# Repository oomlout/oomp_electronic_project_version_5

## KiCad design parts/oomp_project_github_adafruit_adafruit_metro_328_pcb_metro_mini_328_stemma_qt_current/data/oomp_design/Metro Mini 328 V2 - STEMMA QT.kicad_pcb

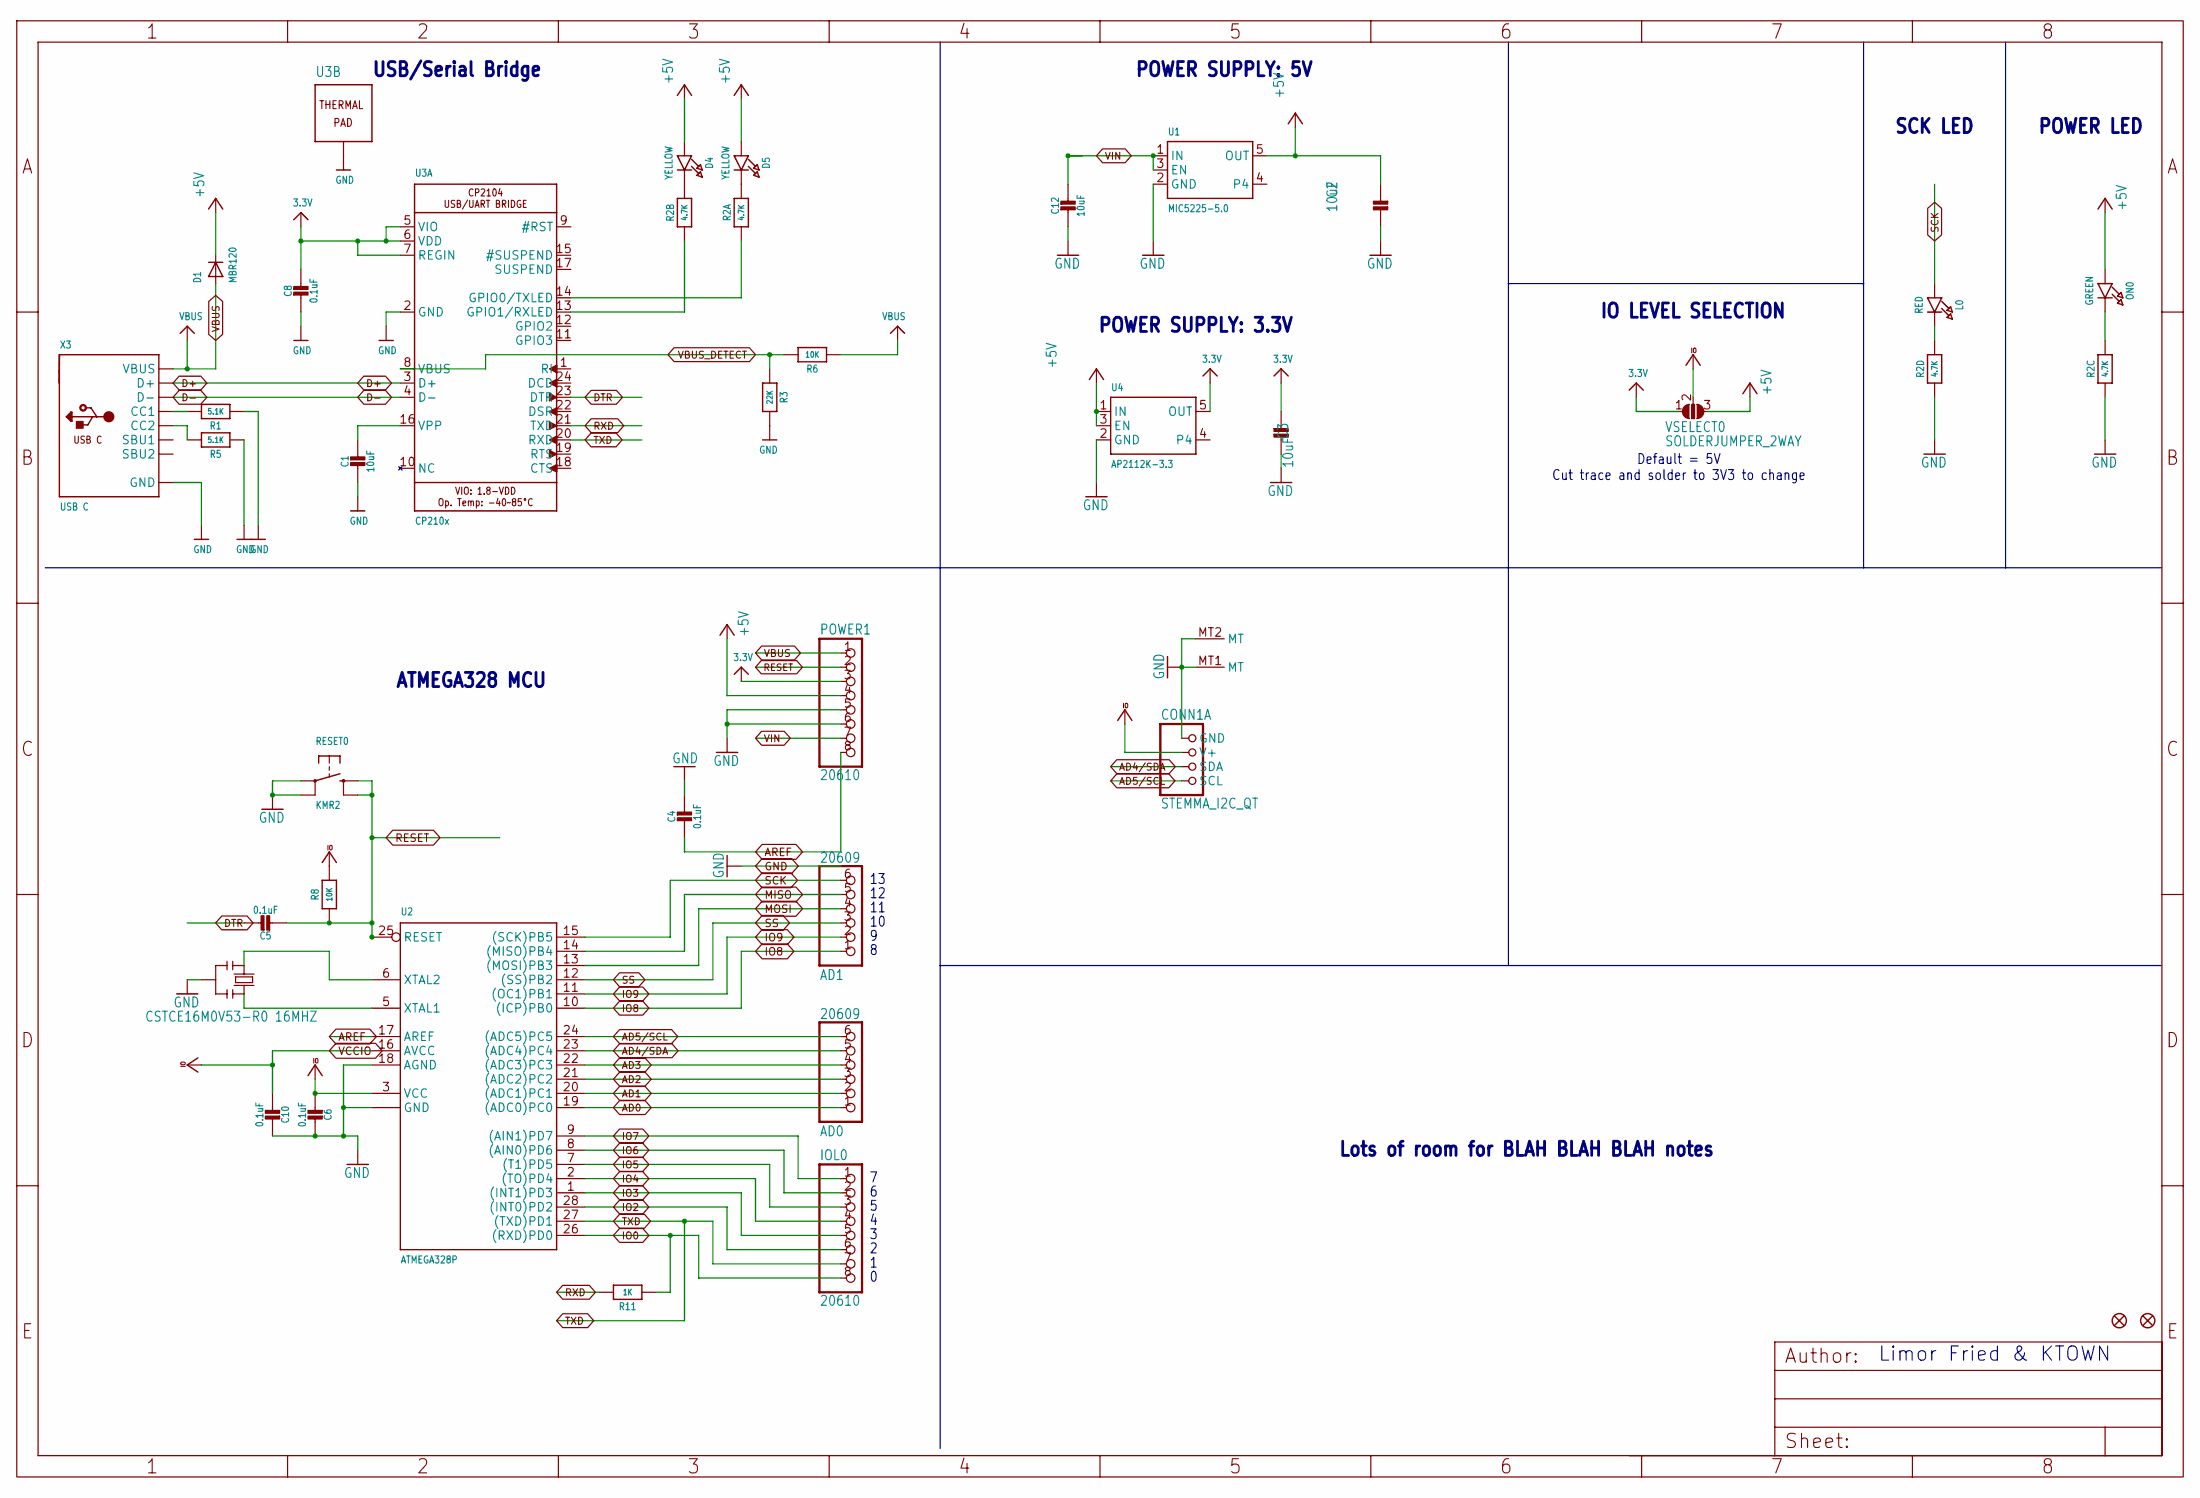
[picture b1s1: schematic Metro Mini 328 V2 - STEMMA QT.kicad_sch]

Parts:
AD0, AD1: 20609; 1X06_ROUND
C1, C2, C3, C12: 10uF; 0805-NO
C4, C5, C6, C8, C10: 0.1uF; 0603-NO
CONN1: STEMMA_I2C_QT; JST_SH4
D1: MBR120; SOD-123FL
D4, D5: YELLOW; CHIPLED_0603_NOOUTLINE
FD1, FD2: FIDUCIAL_1MM
IOL0: 20610; 1X08_ROUND
L0: RED; CHIPLED_0603_NOOUTLINE
ON0: GREEN; CHIPLED_0603_NOOUTLINE
POWER1: 20610; 1X08_ROUND_70
R1, R5: 5.1K; 0603-NO
R2: 4.7K; RESPACK_4X0603
R3: 22K; 0603-NO
R6, R8: 10K; 0603-NO
R11: 1K; 0603-NO
RESET0: KMR2; BTN_KMR2_4.6X2.8
U1: MIC5225-5.0; SOT23-5
U2: ATMEGA328P; QFN28_4MM_.45MM
U3: CP210x; QFN24_4MM_SMSC
U4: AP2112K-3.3; SOT23-5
VSELECT0: SOLDERJUMPER_2WAY; SOLDERJUMPER_2WAY_OPEN_NOPASTE
X3: USB C; USB_C_CUSB31-CFM2AX-01-X
Y2: CSTCE16M0V53-R0 16MHZ; RESONATOR

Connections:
3.3V: C3.2, C8.1, POWER1.3, U3.5 (VIO), U3.6 (VDD), U3.7 (REGIN), U4.5 (OUT), VSELECT0.1
+5V: C2.2, D1.C, D4.A, D5.A, ON0.A, POWER1.4, U1.5 (OUT), U4.1 (IN), U4.3 (EN), VSELECT0.3
AD0: AD0.1, U2.19 ((ADC0)PC0)
AD1: AD0.2, U2.20 ((ADC1)PC1)
AD2: AD0.3, U2.21 ((ADC2)PC2)
AD3: AD0.4, U2.22 ((ADC3)PC3)
AD4/SDA: AD0.5, CONN1.3 (SDA), U2.23 ((ADC4)PC4)
AD5/SCL: AD0.6, CONN1.4 (SCL), U2.24 ((ADC5)PC5)
AREF: C4.2, POWER1.8, U2.17 (AREF)
D+: U3.3 (D+), X3.A6 (D+), X3.B6 (D+)
D-: U3.4 (D-), X3.A7 (D-), X3.B7 (D-)
DTR: C5.1, U3.23 (DTR)
GND: C1.2, C2.1, C3.1, C4.1, C6.1, C8.2, C10.1, C12.2, CONN1.1 (GND), CONN1.MT1 (MT), CONN1.MT2 (MT), POWER1.5, POWER1.6, R1.1, R2.3 (1), R2.4 (1), R3.1, R5.1, RESET0.A, RESET0.A' (P1), U1.2 (GND), U2.4 (GND), U2.18 (AGND), U2.29 (GND), U3.2 (GND), U3.THERM (TP), U4.2 (GND), X3.A1B12 (GND), X3.B1A12 (GND), Y2.2
IO0: IOL0.8, R11.1, U2.26 ((RXD)PD0)
IO2: IOL0.6, U2.28 ((INT0)PD2)
IO3: IOL0.5, U2.1 ((INT1)PD3)
IO4: IOL0.4, U2.2 ((TO)PD4)
IO5: IOL0.3, U2.7 ((T1)PD5)
IO6: IOL0.2, U2.8 ((AIN0)PD6)
IO7: IOL0.1, U2.9 ((AIN1)PD7)
IO8: AD1.1, U2.10 ((ICP)PB0)
IO9: AD1.2, U2.11 ((OC1)PB1)
MISO: AD1.5, U2.14 ((MISO)PB4)
MOSI: AD1.4, U2.13 ((MOSI)PB3)
unnamed: L0.C, R2.5 (2)
unnamed: ON0.C, R2.6 (2)
unnamed: R2.1, U3.14 (GPIO0/TXLED)
unnamed: R1.2, X3.A5 (CC1)
unnamed: D4.C, R2.7 (2)
unnamed: D5.C, R2.8 (2)
unnamed: R5.2, X3.B5 (CC2)
unnamed: C1.1, U3.16 (VPP)
unnamed: R2.2 (1), U3.13 (GPIO1/RXLED)
RESET: C5.2, POWER1.2, R8.1, RESET0.B (S), RESET0.B' (S1), U2.25 (RESET)
RXD: R11.2, U3.21 (TXD)
SCK: AD1.6, L0.A, U2.15 ((SCK)PB5)
SS: AD1.3, U2.12 ((SS)PB2)
TXD: IOL0.7, U2.27 ((TXD)PD1), U3.20 (RXD)
VBUS: D1.A, POWER1.1, R6.2, X3.A4B9 (VBUS), X3.B4A9 (VBUS)
VBUS_DETECT: R3.2, R6.1, U3.8 (VBUS)
VCCIO: C6.2, C10.2, CONN1.2 (V+), R8.2, U2.3 (VCC), U2.16 (AVCC), VSELECT0.2
VIN: C12.1, POWER1.7, U1.1 (IN), U1.3 (EN)
XTAL1: U2.5 (XTAL1), Y2.3
XTAL2: U2.6 (XTAL2), Y2.1

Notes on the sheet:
POWER SUPPLY: 5V
SCK LED
POWER LED
Lots of room for BLAH BLAH BLAH notes
Limor Fried & KTOWN
Default = 5V Cut trace and solder to 3V3 to change
USB/Serial Bridge
IO LEVEL SELECTION
ATMEGA328 MCU
POWER SUPPLY: 3.3V

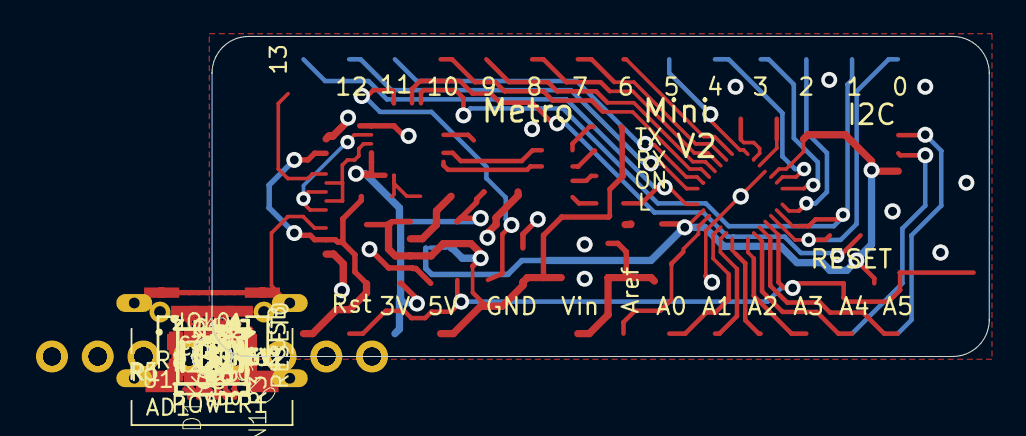
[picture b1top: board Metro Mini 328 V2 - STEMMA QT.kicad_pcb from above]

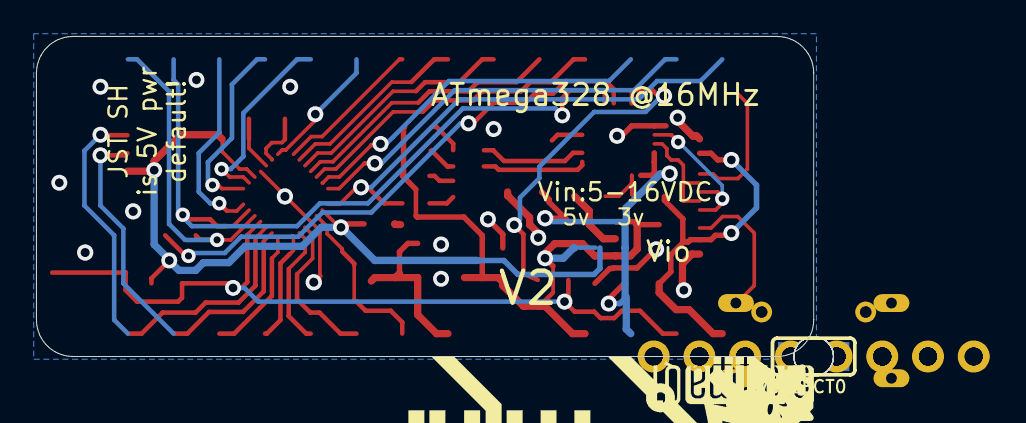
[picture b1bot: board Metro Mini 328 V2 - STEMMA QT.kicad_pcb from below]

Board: 2 copper layers, 43.2 x 17.8 mm, 45 parts (4 on the bottom side), 44 nets.

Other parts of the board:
U$4: PCBFEAT-REV-040
U$5: ADAFRUIT_2.5MM
U$6: STEMMAQT
U$7: METROMINI_SILK
U$10: ADAFRUIT_5MM
UNK_HOLE_0: dummyfp0
UNK_HOLE_1: dummyfp1
UNK_HOLE_2: dummyfp2
UNK_HOLE_3: dummyfp3

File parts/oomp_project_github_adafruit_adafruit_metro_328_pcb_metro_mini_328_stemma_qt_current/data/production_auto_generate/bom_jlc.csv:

Comment,Designator,Footprint,LCSC Part #
,U$5,Metro Mini 328 V2 - STEMMA QT-import-fps:ADAFRUIT_2.5MM,
,U$10,Metro Mini 328 V2 - STEMMA QT-import-fps:ADAFRUIT_5MM,
,U$7,Metro Mini 328 V2 - STEMMA QT-import-fps:METROMINI_SILK,
,U$4,Metro Mini 328 V2 - STEMMA QT-import-fps:PCBFEAT-REV-040,
,VSELECT0,Metro Mini 328 V2 - STEMMA QT-import-fps:SOLDERJUMPER_2WAY_OPEN_NOPASTE,
,U$6,Metro Mini 328 V2 - STEMMA QT-import-fps:STEMMAQT,
0.1uF,"C4,C5,C6,C8,C10",Metro Mini 328 V2 - STEMMA QT-import-fps:0603-NO,C14663
10K,"R6,R8",Metro Mini 328 V2 - STEMMA QT-import-fps:0603-NO,C98220
10uF,"C1,C2,C3,C12",Metro Mini 328 V2 - STEMMA QT-import-fps:0805-NO,
1K,R11,Metro Mini 328 V2 - STEMMA QT-import-fps:0603-NO,C2907002
20609,"AD0,AD1",Metro Mini 328 V2 - STEMMA QT-import-fps:1X06_ROUND,C37208
20610,IOL0,Metro Mini 328 V2 - STEMMA QT-import-fps:1X08_ROUND,C492421
20610,POWER1,Metro Mini 328 V2 - STEMMA QT-import-fps:1X08_ROUND_70,C492421
22K,R3,Metro Mini 328 V2 - STEMMA QT-import-fps:0603-NO,C31850
4.7K,R2,Metro Mini 328 V2 - STEMMA QT-import-fps:RESPACK_4X0603,C23162
5.1K,"R1,R5",Metro Mini 328 V2 - STEMMA QT-import-fps:0603-NO,C23186
AP2112K-3.3,U4,Metro Mini 328 V2 - STEMMA QT-import-fps:SOT23-5,
ATMEGA328P,U2,Metro Mini 328 V2 - STEMMA QT-import-fps:QFN28_4MM_.45MM,
CP210x,U3,Metro Mini 328 V2 - STEMMA QT-import-fps:QFN24_4MM_SMSC,
CSTCE16M0V53-R0 16MHZ,Y2,Metro Mini 328 V2 - STEMMA QT-import-fps:RESONATOR,
FIDUCIAL_1MM,"FD1,FD2",Metro Mini 328 V2 - STEMMA QT-import-fps:FIDUCIAL_1MM,
GREEN,ON0,Metro Mini 328 V2 - STEMMA QT-import-fps:CHIPLED_0603_NOOUTLINE,
KMR2,RESET0,Metro Mini 328 V2 - STEMMA QT-import-fps:BTN_KMR2_4.6X2.8,
MBR120,D1,Metro Mini 328 V2 - STEMMA QT-import-fps:SOD-123FL,
MIC5225-5.0,U1,Metro Mini 328 V2 - STEMMA QT-import-fps:SOT23-5,
RED,L0,Metro Mini 328 V2 - STEMMA QT-import-fps:CHIPLED_0603_NOOUTLINE,
STEMMA_I2C_QT,CONN1,Metro Mini 328 V2 - STEMMA QT-import-fps:JST_SH4,C160404
USB C,X3,Metro Mini 328 V2 - STEMMA QT-import-fps:USB_C_CUSB31-CFM2AX-01-X,
YELLOW,"D4,D5",Metro Mini 328 V2 - STEMMA QT-import-fps:CHIPLED_0603_NOOUTLINE,

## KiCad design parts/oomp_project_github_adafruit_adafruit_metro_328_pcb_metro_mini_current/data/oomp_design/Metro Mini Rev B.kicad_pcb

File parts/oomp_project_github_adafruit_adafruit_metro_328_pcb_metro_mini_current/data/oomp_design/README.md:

# OOMP KiCad design copy

Open `Metro Mini Rev B.kicad_pro` (or the `.kicad_pcb` / `.kicad_sch`) in KiCad. Local OOMP libraries are under `libraries/`. Original inputs are preserved in [../original/](../original/).

Only verified unchanged installed KiCad defaults were renamed. Modified, custom, unmatched and unavailable items remain unchanged. Soldering variants are never swapped during conversion. Existing pad coordinates, nets and UUIDs are preserved.

See [conversion_report.yaml](conversion_report.yaml) for every conversion and skip. Copy this directory before editing; regeneration refuses to overwrite edited design files.

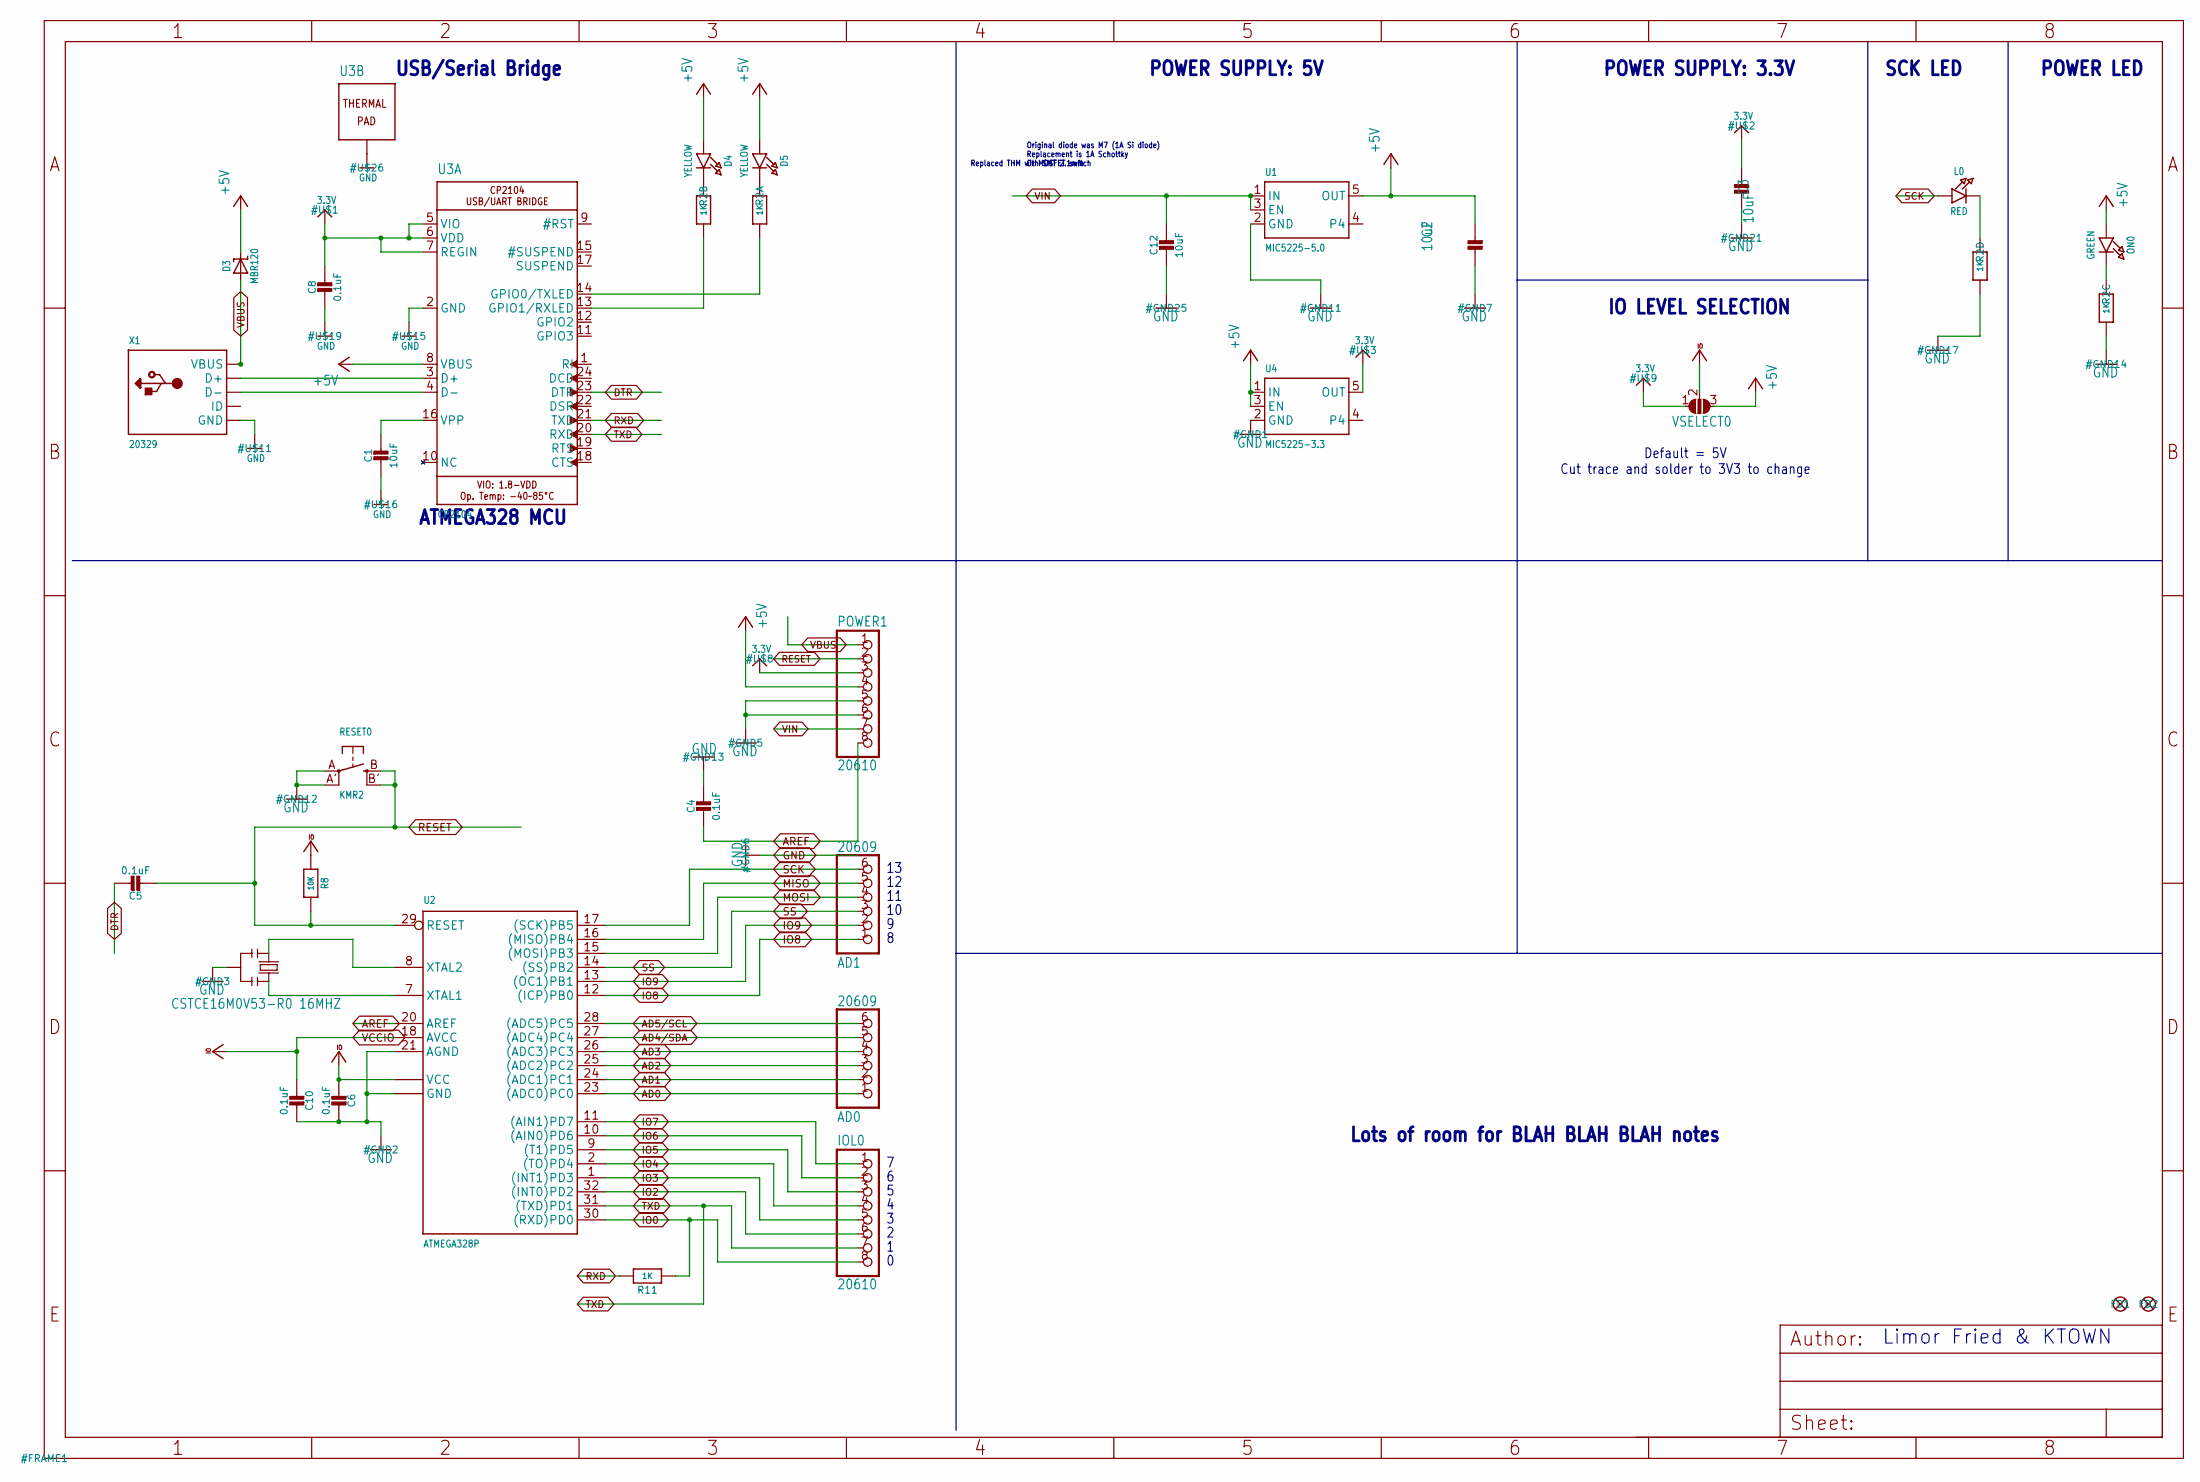
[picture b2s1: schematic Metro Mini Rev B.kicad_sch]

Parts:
AD0, AD1: 20609; 1X06_ROUND
C1, C2, C3, C12: 10uF; 0805-NO
C4, C6, C8, C10: 0.1uF; 0805-NO
C5: 0.1uF; _0805MP
D3: MBR120; SOD-123
D4, D5: YELLOW; CHIPLED_0805_NOOUTLINE
FD1, FD2: FIDUCIAL""; FIDUCIAL_1MM
IOL0: 20610; 1X08_ROUND
L0: RED; CHIPLED_0805_NOOUTLINE
ON0: GREEN; CHIPLED_0805_NOOUTLINE
POWER1: 20610; 1X08_ROUND_70
R2: 1K; RESPACK_4X0603
R8: 10K; 0805-NO
R11: 1K; 0805-NO
RESET0: KMR2; BTN_KMR2_4.6X2.8
U1: MIC5225-5.0; SOT23-5
U2: ATMEGA328P; MLF32-TH
U3: CP2104; QFN24_4MM_SMSC
U4: MIC5225-3.3; SOT23-5
VSELECT0: SOLDERJUMPER_2WAY; SOLDERJUMPER_2WAY_OPEN_NOPASTE
X1: 20329; 4UCONN_20329_V2
Y2: CSTCE16M0V53-R0 16MHZ; RESONATOR

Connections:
3.3V: C3.2, C8.1, POWER1.3, U3.5 (VIO), U3.6 (VDD), U3.7 (REGIN), U4.5 (OUT), VSELECT0.1
+5V: C2.2, D3.C, D4.A, D5.A, ON0.A, POWER1.4, U1.5 (OUT), U3.8 (VBUS), U4.1 (IN), U4.3 (EN), VSELECT0.3
AD0: AD0.1, U2.23 ((ADC0)PC0)
AD1: AD0.2, U2.24 ((ADC1)PC1)
AD2: AD0.3, U2.25 ((ADC2)PC2)
AD3: AD0.4, U2.26 ((ADC3)PC3)
AD4/SDA: AD0.5, U2.27 ((ADC4)PC4)
AD5/SCL: AD0.6, U2.28 ((ADC5)PC5)
AREF: C4.2, POWER1.8, U2.20 (AREF)
DTR: C5.1, U3.23 (DTR)
GND: C1.2, C2.1, C3.1, C4.1, C6.1, C8.2, C10.1, C12.2, POWER1.5, POWER1.6, R2.3 (1), R2.4 (1), RESET0.A, RESET0.A' (P1), U1.2 (GND), U2.3 (GND), U2.5 (GND), U2.21 (AGND), U2.TH (GND), U3.2 (GND), U3.THERM (TP), U4.2 (GND), X1.BASE@1 (GND), X1.BASE@2 (GND), X1.GND, X1.SPRT@1 (GND), X1.SPRT@2 (GND), X1.SPRT@3 (GND), X1.SPRT@4 (GND), Y2.2
IO0: IOL0.8, R11.1, U2.30 ((RXD)PD0)
IO2: IOL0.6, U2.32 ((INT0)PD2)
IO3: IOL0.5, U2.1 ((INT1)PD3)
IO4: IOL0.4, U2.2 ((TO)PD4)
IO5: IOL0.3, U2.9 ((T1)PD5)
IO6: IOL0.2, U2.10 ((AIN0)PD6)
IO7: IOL0.1, U2.11 ((AIN1)PD7)
IO8: AD1.1, U2.12 ((ICP)PB0)
IO9: AD1.2, U2.13 ((OC1)PB1)
MISO: AD1.5, U2.16 ((MISO)PB4)
MOSI: AD1.4, U2.15 ((MOSI)PB3)
unnamed: L0.C, R2.5 (2)
unnamed: ON0.C, R2.6 (2)
unnamed: R2.1, U3.14 (GPIO0/TXLED)
unnamed: D4.C, R2.7 (2)
unnamed: D5.C, R2.8 (2)
unnamed: U3.3 (D+), X1.D+
unnamed: U3.4 (D-), X1.D-
unnamed: C1.1, U3.16 (VPP)
unnamed: R2.2 (1), U3.13 (GPIO1/RXLED)
RESET: C5.2, POWER1.2, R8.1, RESET0.B (S), RESET0.B' (S1), U2.29 (RESET)
RXD: R11.2, U3.21 (TXD)
SCK: AD1.6, L0.A, U2.17 ((SCK)PB5)
SS: AD1.3, U2.14 ((SS)PB2)
TXD: IOL0.7, U2.31 ((TXD)PD1), U3.20 (RXD)
VBUS: D3.A, POWER1.1, X1.VBUS
VCCIO: C6.2, C10.2, R8.2, U2.4 (VCC), U2.6 (VCC), U2.18 (AVCC), VSELECT0.2
VIN: C12.1, POWER1.7, U1.1 (IN), U1.3 (EN)
XTAL1: U2.7 (XTAL1), Y2.3
XTAL2: U2.8 (XTAL2), Y2.1

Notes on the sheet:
Limor Fried & KTOWN
Original diode was M7 (1A Si diode) Replacement is 1A Schottky Or MOSFET switch
USB/Serial Bridge
Default = 5V Cut trace and solder to 3V3 to change
POWER SUPPLY: 3.3V
POWER LED
Lots of room for BLAH BLAH BLAH notes
Replaced THM with SMT 2.1mm
IO LEVEL SELECTION
POWER SUPPLY: 5V
ATMEGA328 MCU
SCK LED

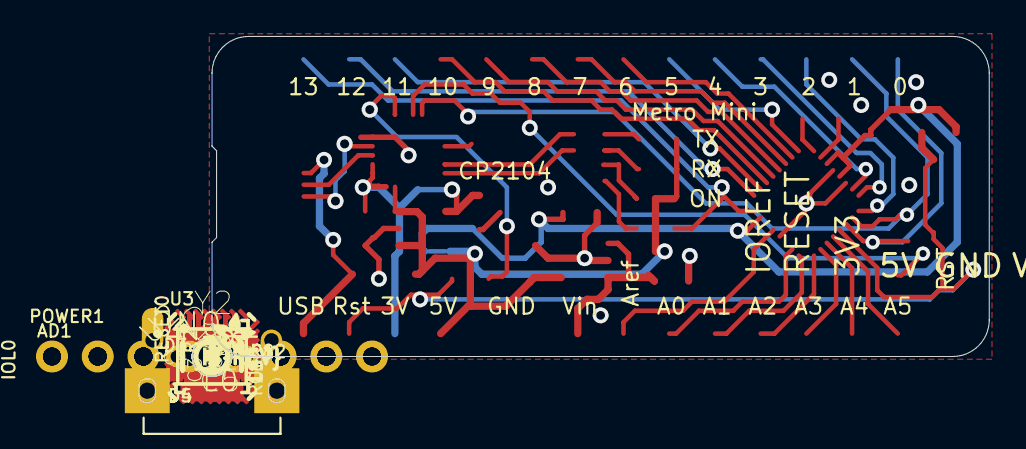
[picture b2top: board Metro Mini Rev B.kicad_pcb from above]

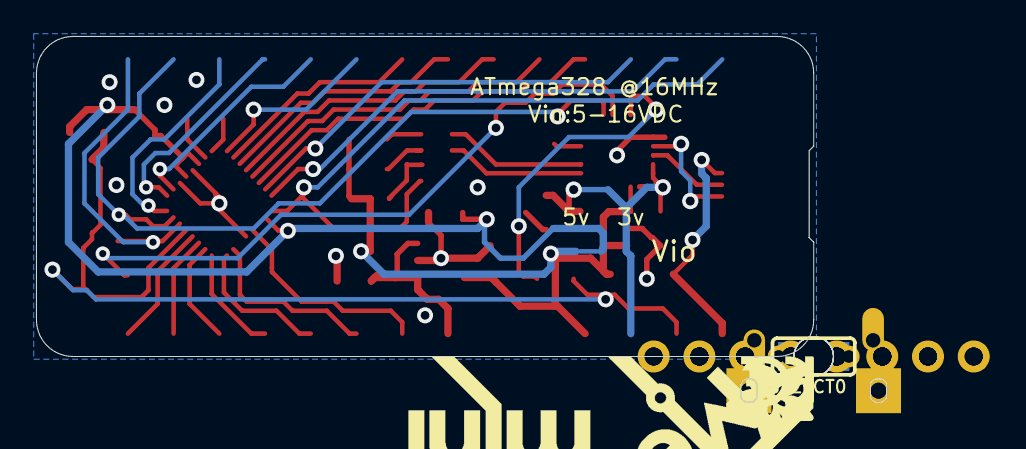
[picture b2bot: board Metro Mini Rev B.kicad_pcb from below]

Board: 2 copper layers, 43.2 x 17.8 mm, 41 parts (5 on the bottom side), 41 nets.

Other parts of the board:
U$4: PCBFEAT-REV-040
U$5: ADAFRUIT_2.5MM
U$7: METROMINI_SILK
U$10: ADAFRUIT_5MM
U$12: SYMBOL_CE_TINY
U$14: SYMBOL_FCC_TINY
UNK_HOLE_0: dummyfp0
UNK_HOLE_1: dummyfp1
UNK_HOLE_2: dummyfp2
UNK_HOLE_3: dummyfp3

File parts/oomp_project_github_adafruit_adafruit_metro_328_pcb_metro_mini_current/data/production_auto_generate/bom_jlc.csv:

Comment,Designator,Footprint,LCSC Part #
,U$5,Metro Mini Rev B-import-fps:ADAFRUIT_2.5MM,
,U$10,Metro Mini Rev B-import-fps:ADAFRUIT_5MM,
,U$7,Metro Mini Rev B-import-fps:METROMINI_SILK,
,U$4,Metro Mini Rev B-import-fps:PCBFEAT-REV-040,
,VSELECT0,Metro Mini Rev B-import-fps:SOLDERJUMPER_2WAY_OPEN_NOPASTE,
,U$12,Metro Mini Rev B-import-fps:SYMBOL_CE_TINY,
,U$14,Metro Mini Rev B-import-fps:SYMBOL_FCC_TINY,
0.1uF,"C4,C6,C8,C10",Metro Mini Rev B-import-fps:0805-NO,
0.1uF,C5,Metro Mini Rev B-import-fps:_0805MP,
10K,R8,Metro Mini Rev B-import-fps:0805-NO,C17414
10uF,"C1,C2,C3,C12",Metro Mini Rev B-import-fps:0805-NO,
1K,R11,Metro Mini Rev B-import-fps:0805-NO,C17513
1K,R2,Metro Mini Rev B-import-fps:RESPACK_4X0603,C2907002
20329,X1,Metro Mini Rev B-import-fps:4UCONN_20329_V2,
20609,"AD0,AD1",Metro Mini Rev B-import-fps:1X06_ROUND,C37208
20610,IOL0,Metro Mini Rev B-import-fps:1X08_ROUND,C492421
20610,POWER1,Metro Mini Rev B-import-fps:1X08_ROUND_70,C492421
ATMEGA328P,U2,Metro Mini Rev B-import-fps:MLF32-TH,
CP2104,U3,Metro Mini Rev B-import-fps:QFN24_4MM_SMSC,
CSTCE16M0V53-R0 16MHZ,Y2,Metro Mini Rev B-import-fps:RESONATOR,
"FIDUCIAL""""","FD1,FD2",Metro Mini Rev B-import-fps:FIDUCIAL_1MM,
GREEN,ON0,Metro Mini Rev B-import-fps:CHIPLED_0805_NOOUTLINE,
KMR2,RESET0,Metro Mini Rev B-import-fps:BTN_KMR2_4.6X2.8,
MBR120,D3,Metro Mini Rev B-import-fps:SOD-123,
MIC5225-3.3,U4,Metro Mini Rev B-import-fps:SOT23-5,
MIC5225-5.0,U1,Metro Mini Rev B-import-fps:SOT23-5,
RED,L0,Metro Mini Rev B-import-fps:CHIPLED_0805_NOOUTLINE,
YELLOW,"D4,D5",Metro Mini Rev B-import-fps:CHIPLED_0805_NOOUTLINE,

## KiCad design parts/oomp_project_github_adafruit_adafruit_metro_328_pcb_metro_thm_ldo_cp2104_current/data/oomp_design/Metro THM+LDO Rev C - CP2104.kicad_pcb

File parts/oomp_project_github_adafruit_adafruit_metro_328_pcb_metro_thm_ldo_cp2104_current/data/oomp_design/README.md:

# OOMP KiCad design copy

Open `Metro THM+LDO Rev C - CP2104.kicad_pro` (or the `.kicad_pcb` / `.kicad_sch`) in KiCad. Local OOMP libraries are under `libraries/`. Original inputs are preserved in [../original/](../original/).

Only verified unchanged installed KiCad defaults were renamed. Modified, custom, unmatched and unavailable items remain unchanged. Soldering variants are never swapped during conversion. Existing pad coordinates, nets and UUIDs are preserved.

See [conversion_report.yaml](conversion_report.yaml) for every conversion and skip. Copy this directory before editing; regeneration refuses to overwrite edited design files.

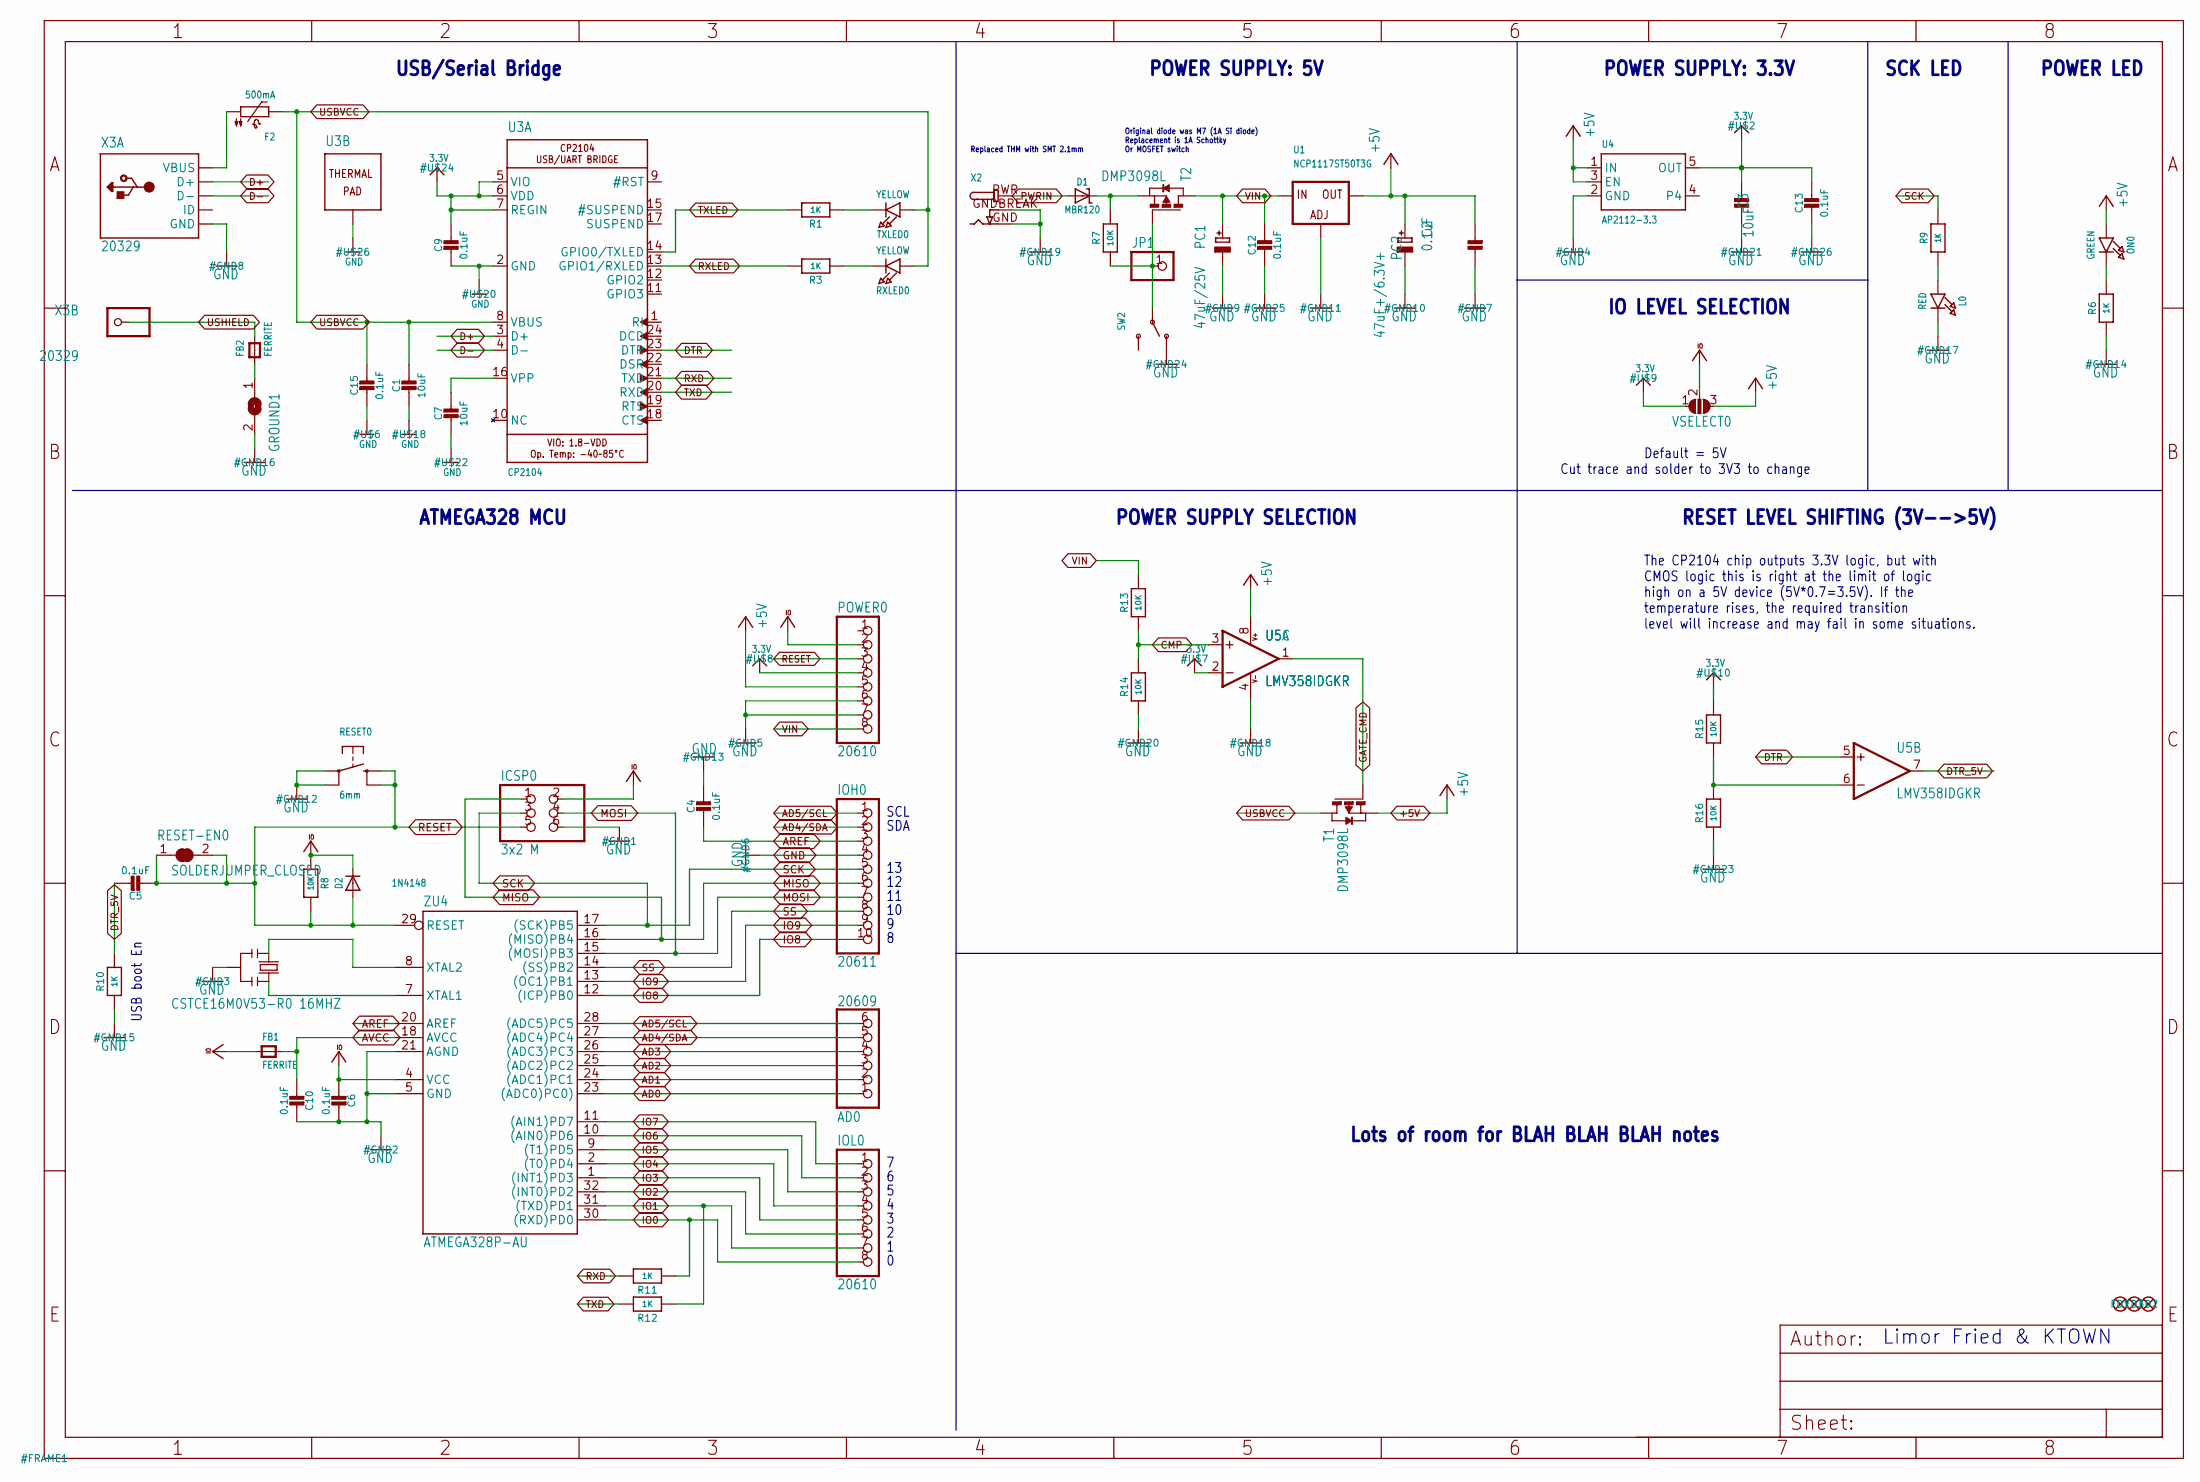
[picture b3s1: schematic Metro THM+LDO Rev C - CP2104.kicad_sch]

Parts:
AD0: 20609; 1X06_OVAL
C1, C3, C7: 10uF; 0805-NO
C2, C4, C5, C6, C9, C12, C13, C15: 0.1uF; 0805-NO
C10: 0.1uF; 0805_10MGAP
D1: MBR120; SOD-123
D2: 1N4148; SOD-323
F2: 500mA; 1206-NO
FB1, FB2: FERRITE; 0805-NO
FD1, FD2, FD3: FIDUCIAL_1MM
GROUND1: SJ
ICSP0: 3x2 M; 2X03_ROUND_70MIL
IOH0: 20611; 1X10_OVAL
IOL0: 20610; 1X08_OVAL
JP1: HEADER-1X1ROUND; 1X01_ROUND
L0: RED; CHIPLED_0805_NOOUTLINE
ON0: GREEN; CHIPLED_0805_NOOUTLINE
PC1: 47uF/25V; PANASONIC_D
PC2: 47uF+/6.3V+; PANASONIC_D
POWER0: 20610; 1X08_OVAL
R1, R3, R6, R9, R10, R11, R12: 1K; 0805-NO
R7, R13, R14, R15, R16: 10K; 0805-NO
R8: 10K; _0805MP
RESET0: 6mm; EVQ-Q2
RESET-EN0: SOLDERJUMPER_CLOSED; SOLDERJUMPER_CLOSEDWIRE
RXLED0: YELLOW; CHIPLED_0805_NOOUTLINE
SW2: SWITCH_SPDT; SPDT_SMT_SSSS811101
T1, T2: DMP3098L; SOT-23
TXLED0: YELLOW; CHIPLED_0805_NOOUTLINE
U1: NCP1117ST50T3G; SOT223-R
U3: CP2104; QFN24_4MM_SMSC
U4: AP2112-3.3; SOT23-5
U5: LMV358IDGKR; MSOP08
VSELECT0: SOLDERJUMPER_2WAY; SOLDERJUMPER_2WAY_OPEN_NOPASTE
X2: DCBARRELPTH; DCJACK_2MM_PTH
X3: 20329; 4UCONN_20329_V2
Y2: CSTCE16M0V53-R0 16MHZ; RESONATOR
ZU4: ATMEGA328P-AU; TQFP32-08

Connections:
3.3V: C3.2, C9.1, C13.1, POWER0.4, R15.2, U3.5 (VIO), U3.6 (VDD), U3.7 (REGIN), U4.5 (OUT), U5.2 (-IN), VSELECT0.1
+5V: C2.2, ON0.A, PC2.+, POWER0.5, T1.2 (S), U1.2 (OUT), U1.4 (OUT), U4.1 (IN), U4.3 (EN), U5.8 (V+), VSELECT0.3
AD0: AD0.1, ZU4.23 ((ADC0)PC0))
AD1: AD0.2, ZU4.24 ((ADC1)PC1)
AD2: AD0.3, ZU4.25 ((ADC2)PC2)
AD3: AD0.4, ZU4.26 ((ADC3)PC3)
AD4/SDA: AD0.5, IOH0.2, ZU4.27 ((ADC4)PC4)
AD5/SCL: AD0.6, IOH0.1, ZU4.28 ((ADC5)PC5)
AREF: C4.2, IOH0.3, ZU4.20 (AREF)
AVCC: C10.2, FB1.2, ZU4.18 (AVCC)
CMP: R13.1, R14.2, U5.3 (+IN)
D+: U3.3 (D+), X3.D+
D-: U3.4 (D-), X3.D-
DTR: U3.23 (DTR), U5.5 (+IN)
DTR_5V: C5.1, R10.2, U5.7 (OUT)
GATE_CMD: T1.3 (G), U5.1 (OUT)
GND: C1.2, C2.1, C3.1, C4.1, C6.1, C7.2, C9.2, C10.1, C12.2, C13.2, C15.2, GROUND1.2, ICSP0.6, IOH0.4, L0.C, PC1.-, PC2.-, POWER0.6, POWER0.7, R6.1, R10.1, R14.1, R16.1, RESET0.A, RESET0.A' (P1), SW2.A (O), U1.1 (ADJ), U3.2 (GND), U3.THERM (TP), U4.2 (GND), U5.4 (V-), X2.GND, X2.GNDBREAK, X3.GND, Y2.2, ZU4.5 (GND), ZU4.21 (AGND)
IO0: IOL0.8, R11.1, ZU4.30 ((RXD)PD0)
IO1: IOL0.7, R12.1, ZU4.31 ((TXD)PD1)
IO2: IOL0.6, ZU4.32 ((INT0)PD2)
IO3: IOL0.5, ZU4.1 ((INT1)PD3)
IO4: IOL0.4, ZU4.2 ((T0)PD4)
IO5: IOL0.3, ZU4.9 ((T1)PD5)
IO6: IOL0.2, ZU4.10 ((AIN0)PD6)
IO7: IOL0.1, ZU4.11 ((AIN1)PD7)
IO8: IOH0.10, ZU4.12 ((ICP)PB0)
IO9: IOH0.9, ZU4.13 ((OC1)PB1)
MISO: ICSP0.1, IOH0.6, ZU4.16 ((MISO)PB4)
MOSI: ICSP0.4, IOH0.7, ZU4.15 ((MOSI)PB3)
unnamed: L0.A, R9.1
unnamed: FB2.1, GROUND1.1
unnamed: ON0.C, R6.2
unnamed: R3.1, RXLED0.C
unnamed: R1.1, TXLED0.C
unnamed: R15.1, R16.2, U5.6 (-IN)
unnamed: JP1.1, R7.1, SW2.B, T2.3 (G)
unnamed: D1.C, R7.2, T2.2 (S)
unnamed: C7.1, U3.16 (VPP)
PWRIN: D1.A, X2.PWR
RESET: C5.2, D2.A, ICSP0.5, POWER0.3, R8.1, RESET0.B (S), RESET0.B' (S1), RESET-EN0.1, RESET-EN0.2, ZU4.29 (RESET)
RXD: R11.2, U3.21 (TXD)
RXLED: R3.2, U3.13 (GPIO1/RXLED)
SCK: ICSP0.3, IOH0.5, R9.2, ZU4.17 ((SCK)PB5)
SS: IOH0.8, ZU4.14 ((SS)PB2)
TXD: R12.2, U3.20 (RXD)
TXLED: R1.2, U3.14 (GPIO0/TXLED)
USBVCC: C1.1, C15.1, F2.2, RXLED0.A, T1.1 (D), TXLED0.A, U3.8 (VBUS)
USHIELD: FB2.2, X3.BASE@1 (1), X3.BASE@2 (1), X3.SPRT@1 (1), X3.SPRT@2 (1), X3.SPRT@3 (1), X3.SPRT@4 (1)
VBUS: F2.1, X3.VBUS
VCCIO: C6.2, D2.C, FB1.1, ICSP0.2, POWER0.2, R8.2, VSELECT0.2, ZU4.4 (VCC)
VIN: C12.1, PC1.+, POWER0.8, R13.2, T2.1 (D), U1.3 (IN)
XTAL1: Y2.3, ZU4.7 (XTAL1)
XTAL2: Y2.1, ZU4.8 (XTAL2)

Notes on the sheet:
POWER LED
POWER SUPPLY: 5V
Lots of room for BLAH BLAH BLAH notes
RESET LEVEL SHIFTING (3V-->5V)
The CP2104 chip outputs 3.3V logic, but with CMOS logic this is right at the limit of logic high on a 5V device (5V*0.7=3.5V). If the temperature rises, the required transition level will increase and may fail in some situations.
Limor Fried & KTOWN
IO LEVEL SELECTION
SDA
POWER SUPPLY SELECTION
SCL
USB/Serial Bridge
Original diode was M7 (1A Si diode) Replacement is 1A Schottky Or MOSFET switch
ATMEGA328 MCU
SCK LED
Replaced THM with SMT 2.1mm
POWER SUPPLY: 3.3V
USB boot En
Default = 5V Cut trace and solder to 3V3 to change
